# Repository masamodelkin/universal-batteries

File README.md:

# universal-batteries

Are you tired that all of those "wireless" devices actually require wires to charge them? Are you tired of all those wires on your table? Do you want to build a DIY project but you don't know what batteries to use? Or maybe you are not sure if wireless is the solution due to inconveniences with charging? 

If you answered yes to any of that, this project is for you! I personally answered yes to all of them, so I decided to make this modular battery system, so they can be swapped in seconds and no wires will be needed to charge any of the wireless tech that I have (not all of them, but most of them). 

This project introduces a simple design of a battery shell, charger and module that can be inserted into any project (or even existing electronics) to make it support hot-swap batteries and make all project batteries compatible with each other. 

The design features a charging station to charge 3 batteries at a time controlled with an ESP32-C6 allowing wireless control over it, battery shell design supporting 503759 batteries (1200mAh), and a battery bay to integrate into any project. 

This project is a work in progress, none of the electronics have been tested yet, including firmware and PCB. 

Here is the routed PCB for the charger:

## Bill of Materials (BOM)

| Component | Quantity | Unit Price | Total Price | Link |
|-----------|----------|------------|-------------|------|
| PCB (assembled) | 1 | 55.38 USD (35.38 + 20 shipping) | 55.38 USD | - |
| XIAO ESP32-C6 | 1 | 15.63 CAD (8.19 + 7.01 shipping + 0.43 antenna) | 15.63 CAD | [AliExpress](https://www.aliexpress.com/item/1005006935181127.html) |
| JST XH Connector Set (2-pin x3, 3-pin x1, 4-pin x1) | 1 | 6.92 CAD | 6.92 CAD | [AliExpress](https://www.aliexpress.com/item/1005009383841966.html) |
| Battery 503759 (1200mAh) | 3 | 14.94 CAD (pack of 3) | 14.94 CAD | [AliExpress](https://www.aliexpress.com/item/1005007102975858.html) |
| M3x6 Screws | 18 | - | - | - |
| M3x4x5 Heat Inserts | 18 | 7.55 CAD | 7.55 CAD | [AliExpress](https://www.aliexpress.com/item/1005009193787820.html) |
| Pogo Pins Connector 1x4 Male 4mm | 6 | 3.32 CAD | 19.92 CAD | [AliExpress](https://www.aliexpress.com/item/1005005380466642.html) |
| Pogo Pins Connector 1x4 Female 4mm | 6 | 3.48 CAD | 20.88 CAD | [AliExpress](https://www.aliexpress.com/item/1005005380466642.html) |
| Magnets 6x3mm | 18 | 11.24 CAD (4.33 + 6.91 shipping) | 11.24 CAD | [AliExpress](https://www.aliexpress.com/item/1005009258751295.html) |
| Magnets 6x2mm | 4 | 12.09 CAD (2.89 + 9.20 shipping) | 12.09 CAD | [AliExpress](https://www.aliexpress.com/item/1005009461555694.html) |
| PLA Filament | ~150g | Already own | 0.00 | - |
| **TOTAL** | | | **134.42 USD** | |

*Note: Prices include shipping where applicable. Some components may be sold in larger quantities than needed.*

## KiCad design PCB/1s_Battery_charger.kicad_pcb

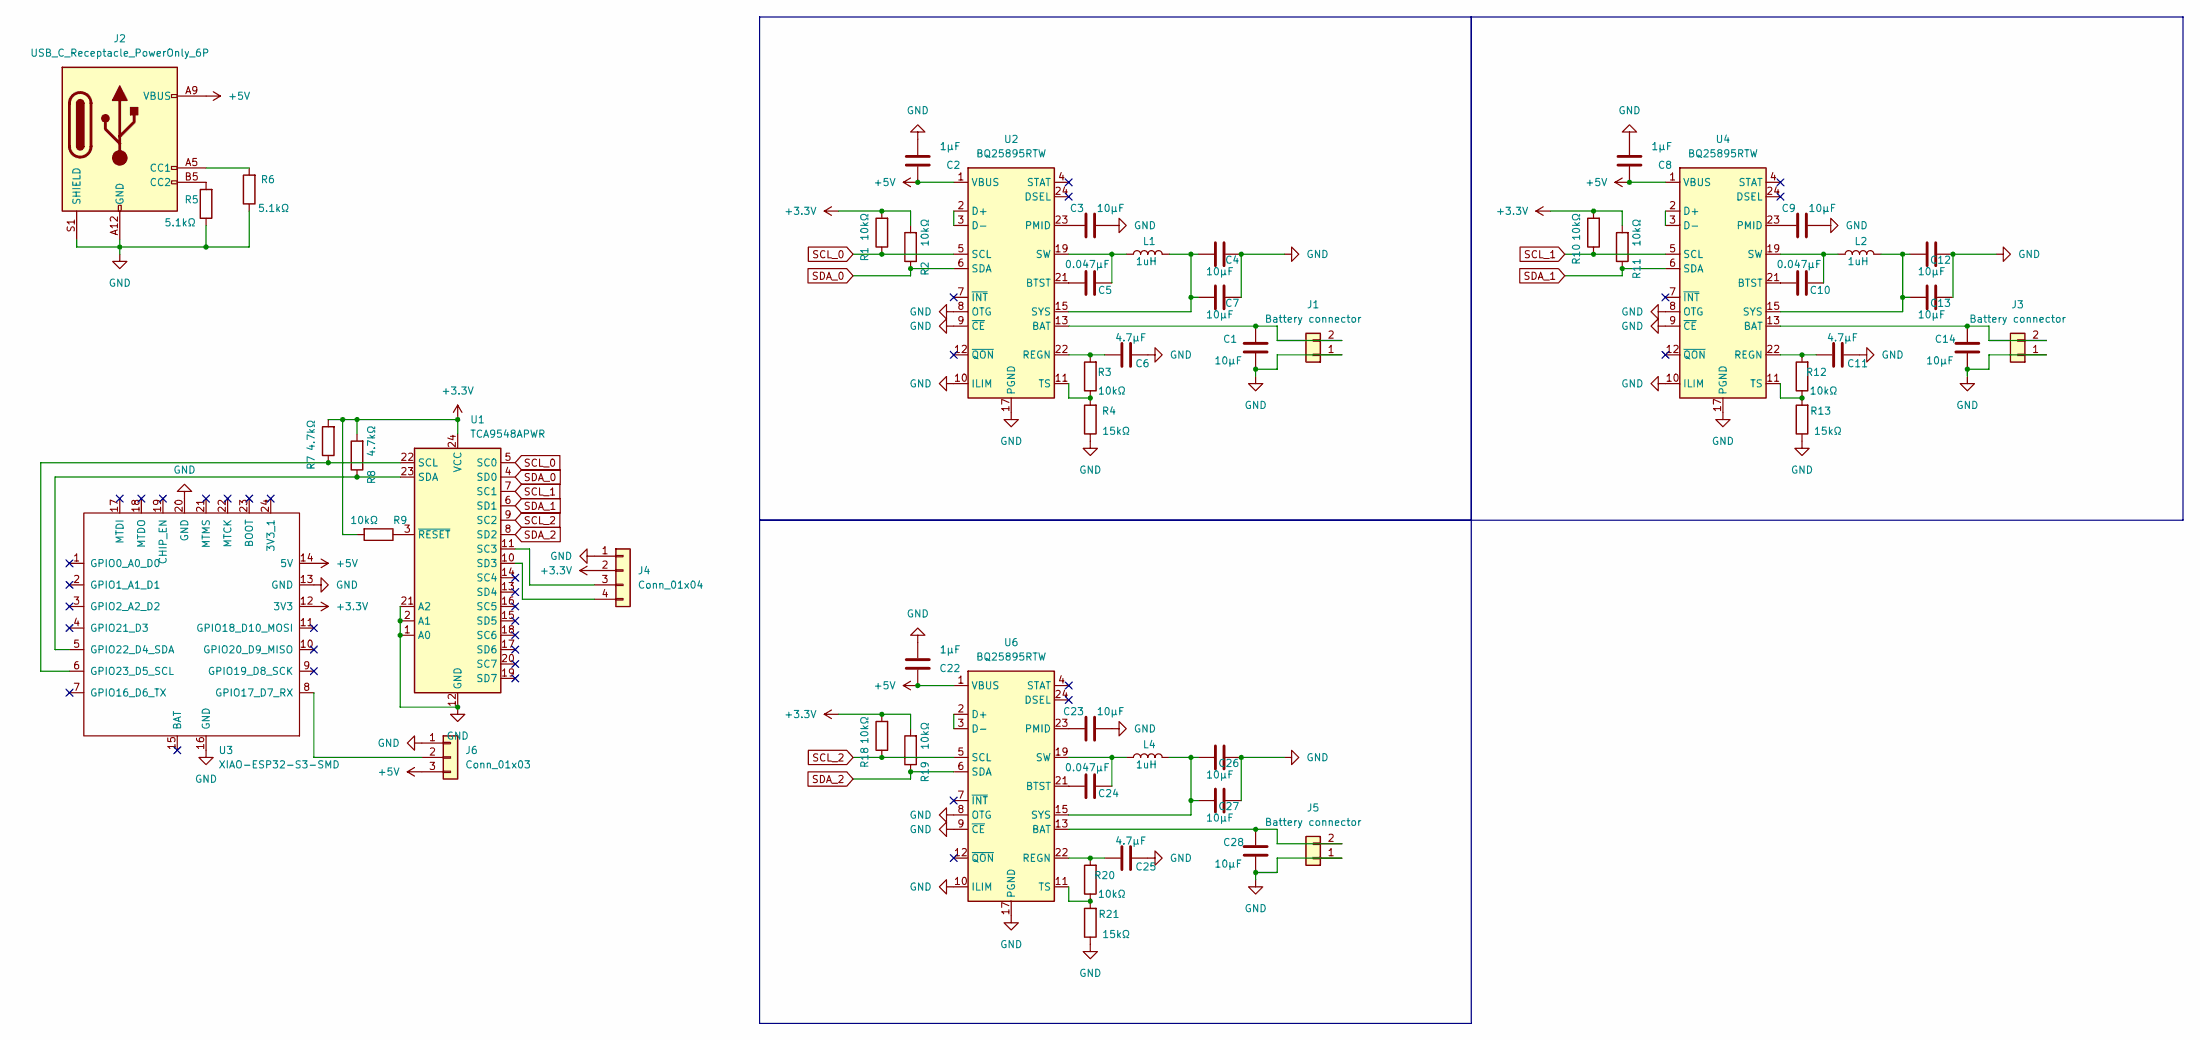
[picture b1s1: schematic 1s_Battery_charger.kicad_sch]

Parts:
C1, C14, C28: 10µF; C_0805_2012Metric
C2, C8, C22: 1μF; C_0805_2012Metric
C3, C4, C7, C9, C12, C13, C23, C26, C27: 10μF; C_0805_2012Metric
C5, C10, C24: 0.047μF; C_0805_2012Metric
C6, C11, C25: 4.7μF; C_0805_2012Metric
J1, J3, J5: Battery connector; JST_XH_B2B-XH-A_1x02_P2.50mm_Vertical
J2: USB_C_Receptacle_PowerOnly_6P; USB_C_Receptacle_GCT_USB4125-xx-x_6P_TopMnt_Horizontal
J4: Conn_01x04; JST_XH_B4B-XH-A_1x04_P2.50mm_Vertical
J6: Conn_01x03; JST_XH_B3B-XH-A_1x03_P2.50mm_Vertical
L1, L2, L4: 1uH; L_Changjiang_FXL0420
R1, R2, R10, R11, R18, R19: 10kΩ; R_1206_3216Metric
R3, R9, R12, R20: 10kΩ; R_0805_2012Metric
R4, R13, R21: 15kΩ; R_0805_2012Metric
R5, R6: 5.1kΩ; R_0603_1608Metric
R7, R8: 4.7kΩ; R_1206_3216Metric
U1: TCA9548APWR; TSSOP-24_4.4x7.8mm_P0.65mm
U2, U4, U6: BQ25895RTW; Texas_RTW_WQFN-24-1EP_4x4mm_P0.5mm_EP2.7x2.7mm_ThermalVias
U3: XIAO-ESP32-S3-SMD; XIAO-ESP32C6-SMD

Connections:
+3.3V: J4.2, R1.2, R2.2, R7.2, R8.2, R9.2, R10.2, R11.2, R18.2, R19.2, U1.24 (VCC), U3.12 (3V3)
+5V: C2.1, C8.1, C22.1, J2.A9 (VBUS), J2.B9 (VBUS), J6.3, U2.1 (VBUS), U3.14 (5V), U4.1 (VBUS), U6.1 (VBUS)
GND: C1.2, C2.2, C3.2, C4.2, C6.1, C7.2, C8.2, C9.2, C11.1, C12.2, C13.2, C14.2, C22.2, C23.2, C25.1, C26.2, C27.2, C28.2, J1.1, J2.A12 (GND), J2.B12 (GND), J2.S1 (SHIELD), J3.1, J4.1, J5.1, J6.1, R4.1, R5.1, R6.1, R13.1, R21.1, U1.1 (A0), U1.2 (A1), U1.12 (GND), U1.21 (A2), U2.8 (OTG), U2.9 (~CE), U2.10 (ILIM), U2.17 (PGND), U2.18 (PGND), U2.25 (PGND), U3.13 (GND), U3.16 (GND), U3.20 (GND), U4.8 (OTG), U4.9 (~CE), U4.10 (ILIM), U4.17 (PGND), U4.18 (PGND), U4.25 (PGND), U6.8 (OTG), U6.9 (~CE), U6.10 (ILIM), U6.17 (PGND), U6.18 (PGND), U6.25 (PGND)
unnamed: C4.1, C7.1, L1.2, U2.15 (SYS), U2.16 (SYS)
unnamed: C5.1, L1.1, U2.19 (SW), U2.20 (SW)
unnamed: C10.1, L2.1, U4.19 (SW), U4.20 (SW)
unnamed: C12.1, C13.1, L2.2, U4.15 (SYS), U4.16 (SYS)
unnamed: C24.1, L4.1, U6.19 (SW), U6.20 (SW)
unnamed: C26.1, C27.1, L4.2, U6.15 (SYS), U6.16 (SYS)
unnamed: C1.1, J1.2, U2.13 (BAT), U2.14 (BAT)
unnamed: J2.A5 (CC1), R6.2
unnamed: J2.B5 (CC2), R5.2
unnamed: C14.1, J3.2, U4.13 (BAT), U4.14 (BAT)
unnamed: J4.3, U1.11 (SC3)
unnamed: J4.4, U1.10 (SD3)
unnamed: C28.1, J5.2, U6.13 (BAT), U6.14 (BAT)
unnamed: J6.2, U3.8 (GPIO17_D7_RX)
unnamed: R7.1, U1.22 (SCL), U3.6 (GPIO23_D5_SCL)
unnamed: R8.1, U1.23 (SDA), U3.5 (GPIO22_D4_SDA)
unnamed: R9.1, U1.3 (~RESET)
unnamed: C5.2, U2.21 (BTST)
unnamed: U2.2 (D+), U2.3 (D-)
unnamed: C3.1, U2.23 (PMID)
unnamed: C6.2, R3.2, U2.22 (REGN)
unnamed: R3.1, R4.2, U2.11 (TS)
unnamed: C10.2, U4.21 (BTST)
unnamed: U4.2 (D+), U4.3 (D-)
unnamed: C9.1, U4.23 (PMID)
unnamed: C11.2, R12.2, U4.22 (REGN)
unnamed: R12.1, R13.2, U4.11 (TS)
unnamed: C24.2, U6.21 (BTST)
unnamed: U6.2 (D+), U6.3 (D-)
unnamed: C23.1, U6.23 (PMID)
unnamed: C25.2, R20.2, U6.22 (REGN)
unnamed: R20.1, R21.2, U6.11 (TS)
SCL_0: R1.1, U1.5 (SC0), U2.5 (SCL)
SCL_1: R10.1, U1.7 (SC1), U4.5 (SCL)
SCL_2: R18.1, U1.9 (SC2), U6.5 (SCL)
SDA_0: R2.1, U1.4 (SD0), U2.6 (SDA)
SDA_1: R11.1, U1.6 (SD1), U4.6 (SDA)
SDA_2: R19.1, U1.8 (SD2), U6.6 (SDA)

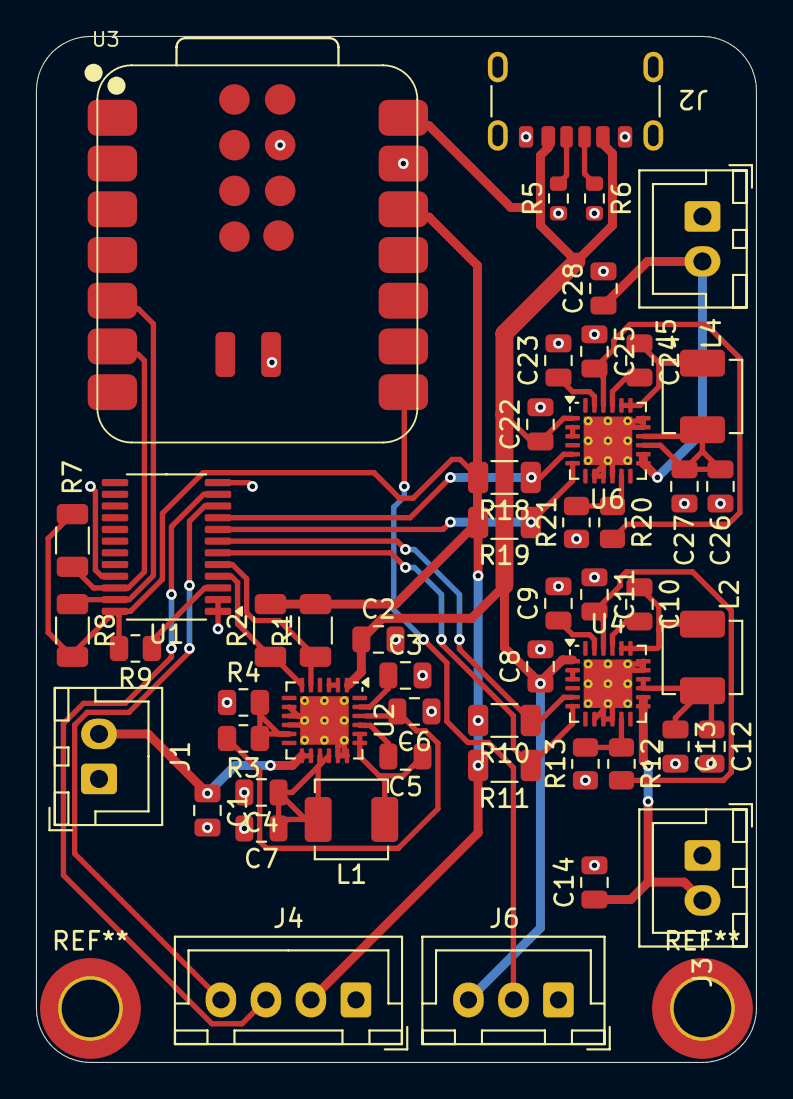
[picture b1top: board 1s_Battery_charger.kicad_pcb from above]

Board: 2 copper layers, 40.0 x 57.0 mm, 52 parts (0 on the bottom side), 41 nets.

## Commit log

2025-07-02 Added images folder, renamed images
2025-07-30 BOM added to README
2025-07-30 added total time spent into JOURNAL
2025-07-31 Fixed the issue with XIAO module being too far from the board edge
